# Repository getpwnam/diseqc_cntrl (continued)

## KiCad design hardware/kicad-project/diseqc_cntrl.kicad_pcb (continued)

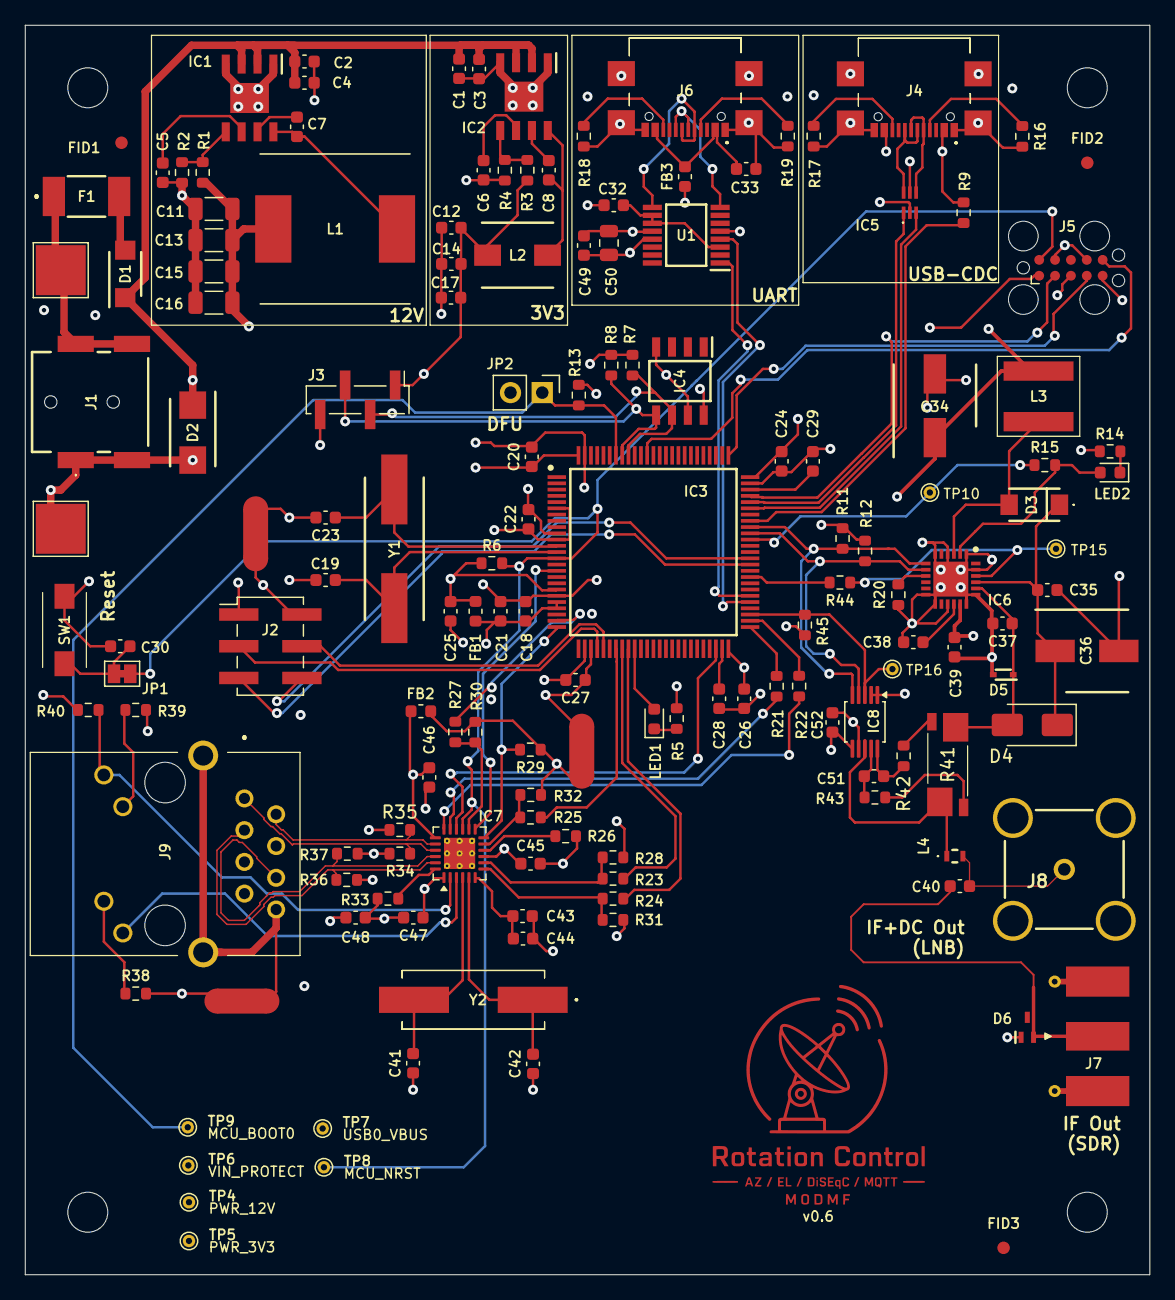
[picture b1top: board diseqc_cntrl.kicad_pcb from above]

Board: 4 copper layers, 90.0 x 100.0 mm, 153 parts (0 on the bottom side), 102 nets.

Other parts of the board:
MOUNT01, MOUNT02, MOUNT03, MOUNT04: MountingHole_3.2mm_M3

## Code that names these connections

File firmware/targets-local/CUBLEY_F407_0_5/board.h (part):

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    as safe "input + pull-up". Subsequent phases flip individual pins to their
    alternate functions as each peripheral is brought up:

      Phase 1  PD8/PD9 USART3 (AF7)              wire protocol @ 921600
      Phase 2  PB0 LED_STATUS (output PP low)    boot double-flash
      Phase 3  PB6/PB7 I2C1 (AF4 OD)             FRAM
      Phase 6  PA8/PC9 I2C3 (AF4 OD), PC8 input  LNBH26 + fault
      Phase 7  PA1/PA2/PA7/PB11-13/PC1/PC4/PC5   RMII to LAN8742A (AF11)
      Later    PD12/PD14/PD15 TIM4 (AF2)         DiSEqC carrier, motor
*/

#ifndef BOARD_H
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/* IO pins assignments.                                                      */
/*===========================================================================*/

/* GPIOA: PA1/PA2/PA7 RMII, PA8 I2C3_SCL, PA9 VBUS_SENSE, PA13/PA14 SWD */
#define GPIOA_PIN0                  0U
#define GPIOA_RMII_REF_CLK          1U
#define GPIOA_RMII_MDIO             2U
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#define GPIOA_SWCLK                 14U
#define GPIOA_PIN15                 15U

/* GPIOB: PB0 LED, PB3 SWO, PB6/PB7 I2C1, PB11-PB13 RMII TX */
#define GPIOB_LED_STATUS            0U
#define GPIOB_PIN1                  1U
#define GPIOB_PIN2                  2U
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#define GPIOB_PIN14                 14U
#define GPIOB_PIN15                 15U

/* GPIOC: PC1/PC4/PC5 RMII, PC8 LNB fault, PC9 I2C3_SDA */
#define GPIOC_PIN0                  0U
#define GPIOC_RMII_MDC              1U
#define GPIOC_PIN2                  2U
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#define GPIOC_PIN14                 14U
#define GPIOC_PIN15                 15U

/* GPIOD: PD8/PD9 USART3 (wire protocol), PD12/PD14/PD15 TIM4 */
#define GPIOD_PIN0                  0U
#define GPIOD_PIN1                  1U
#define GPIOD_PIN2                  2U
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#define GPIOE_PIN14                 14U
#define GPIOE_PIN15                 15U

/* GPIOH: only PH0/PH1 exist on LQFP100 (HSE crystal) */
#define GPIOH_OSC_IN                0U
#define GPIOH_OSC_OUT               1U
#define GPIOH_PIN2                  2U
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 * PUPDR/ODR/AFRL/AFRH encoding.
 *
 * Phase 0 rule: every board-owned peripheral pin is configured as INPUT with
 * PULL-UP so unowned peripherals cannot drive anything. Only SWD (PA13/PA14),
 * SWO (PB3), and OSC (PH0/PH1) are wired to their standard functions from
 * day one.
 */
#define PIN_MODE_INPUT(n)           (0U << ((n) * 2U))
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 * GPIOA setup (Phase 0): all peripheral pins input pull-up; SWD active.
 *
 *  PA0  - PIN0             (input pull-up)
 *  PA1  - RMII_REF_CLK     (alternate 11)
 *  PA2  - RMII_MDIO        (alternate 11, pull-up)
 *  PA3  - PIN3             (input pull-up)
 *  PA4  - PIN4             (input pull-up)
 *  PA5  - PIN5             (input pull-up)
 *  PA6  - PIN6             (input pull-up)
 *  PA7  - RMII_CRS_DV      (alternate 11)
 *  PA8  - I2C3_SCL         (input pull-up, Phase 6 -> AF4 OD)
 *  PA9  - VBUS_SENSE       (input floating, VBUS through 100k series resistor)
 *  PA10 - PIN10            (input floating)
 *  PA11 - USB_FS_DM        (alternate 10)
 *  PA12 - USB_FS_DP        (alternate 10)
 *  PA13 - SWDIO            (alternate 0)
 *  PA14 - SWCLK            (alternate 0)
 *  PA15 - PIN15            (input pull-up)
 */
#define VAL_GPIOA_MODER             (PIN_MODE_INPUT(GPIOA_PIN0)          |  \
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                                     PIN_AFIO_AF(GPIOA_SWCLK, 0U))

/*
 * GPIOB setup (Phase 0): all peripheral pins input pull-up; SWO active.
 *
 *  PB0  - LED_STATUS       (input pull-up, Phase 2 -> output PP low)
 *  PB1  - PIN1             (input pull-up)
 *  PB2  - PIN2             (input pull-up)
 *  PB3  - SWO              (alternate 0)
 *  PB4  - PIN4             (input pull-up)
 *  PB5  - PIN5             (input pull-up)
 *  PB6  - I2C1_SCL         (input pull-up, Phase 3 -> AF4 OD)
 *  PB7  - I2C1_SDA         (input pull-up, Phase 3 -> AF4 OD)
 *  PB8  - PIN8             (input pull-up)
 *  PB9  - PIN9             (input pull-up)
 *  PB10 - PIN10            (input pull-up)
 *  PB11 - RMII_TX_EN       (alternate 11, pull-down)
 *  PB12 - RMII_TXD0        (alternate 11, pull-down)
 *  PB13 - RMII_TXD1        (alternate 11, pull-down)
 *  PB14 - PIN14            (input pull-up)
 *  PB15 - PIN15            (input pull-up)
 */
#define VAL_GPIOB_MODER             (PIN_MODE_INPUT(GPIOB_LED_STATUS)    |  \
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 * GPIOC setup (Phase 0): all peripheral pins input pull-up.
 *
 *  PC0  - PIN0             (input pull-up)
 *  PC1  - RMII_MDC         (alternate 11, pull-up)
 *  PC2  - PIN2             (input pull-up)
 *  PC3  - PIN3             (input pull-up)
 *  PC4  - RMII_RXD0        (alternate 11)
 *  PC5  - RMII_RXD1        (alternate 11)
 *  PC6  - PIN6             (input pull-up)
 *  PC7  - PIN7             (input pull-up)
 *  PC8  - LNB_FLT          (input pull-up)
 *  PC9  - I2C3_SDA         (input pull-up, Phase 6 -> AF4 OD)
 *  PC10 - PIN10            (input pull-up)
 *  PC11 - PIN11            (input pull-up)
 *  PC12 - PIN12            (input pull-up)
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 * GPIOD setup (Phase 0): all peripheral pins input pull-up.
 *
 *  PD0..PD7   PIN0..PIN7   (input pull-up)
 *  PD8  - USART3_TX        (input pull-up, Phase 1 -> AF7)
 *  PD9  - USART3_RX        (input pull-up, Phase 1 -> AF7)
 *  PD10 - PIN10            (input pull-up)
 *  PD11 - PIN11            (input pull-up)
 *  PD12 - TIM4_CH1         (input pull-up, later -> AF2)
 *  PD13 - PIN13            (input pull-up)
 *  PD14 - TIM4_CH3         (input pull-up, later -> AF2)
 *  PD15 - TIM4_CH4         (input pull-up, later -> AF2)
 */
#define VAL_GPIOD_MODER             0x00000000U
#define VAL_GPIOD_OTYPER            0x00000000U
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#define VAL_GPIOG_AFRH              0x00000000U

/*
 * GPIOH setup (LQFP100): only PH0 (OSC_IN) and PH1 (OSC_OUT) are pinned out.
 * ChibiOS PAL leaves them as input floating; the stm32_clock_init() code
 * enables the HSE oscillator via RCC->CR (BYP=0, HSEON=1).
 */
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
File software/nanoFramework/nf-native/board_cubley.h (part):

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 * Board identifier
 */
#define BOARD_M0DMF_CUBLEY_F407
#define BOARD_NAME                  "DiSEqC Controller STM32F407VGT6"

/*
 * USB OTG_FS configuration.
 *
 * The board exposes USB VBUS to PA9 only through R31 (100k pull-up to VBUS,
 * no divider/pull-down). That impedance is too high to reliably trip the
 * STM32F407 OTG_FS A/B-session VBUS comparators, so VBUSASEN/VBUSBSEN never
 * report VBUS valid, the core never asserts the D+ pull-up, and the host
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/*
 * DiSEqC Configuration
 */
#define DISEQC_PWM_DRIVER           PWMD4    // TIM4 for DiSEqC carrier
#define DISEQC_GPT_DRIVER           GPTD5    // TIM5 for bit timing
#define DISEQC_OUTPUT_LINE          PAL_LINE(GPIOD, 12U)  // PD12 = TIM4_CH1

// Note: No motor enable pin - LNBH26 handles power control automatically
// DiSEqC commands control rotor movement directly
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 * LNB Control Configuration (LNBH26PQR via I2C)
 * 
 * LNBH26PQR is controlled via I2C interface:
 * - I2C3: PA8 (SCL), PC9 (SDA)
 * - I2C Address: 0x08 (7-bit)
 * 
 * The LNBH26PQR controls:
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
/*
 * RMII Ethernet Configuration (hardware v0.5)
 * PA1  = REF_CLK
 * PA2  = MDIO
 * PA7  = CRS_DV
 * PC1  = MDC
 * PC4  = RXD0
 * PC5  = RXD1
 * PB11 = TX_EN
 * PB12 = TXD0
 * PB13 = TXD1
 */
#define ETH_RMII_REF_CLK_LINE       PAL_LINE(GPIOA, 1U)
#define ETH_RMII_MDIO_LINE          PAL_LINE(GPIOA, 2U)
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/*
 * Rotator helper signal mapping (feature bring-up)
 */
#define ROTATOR_PWM_A_LINE          PAL_LINE(GPIOD, 14U) // TIM4_CH3
#define ROTATOR_PWM_B_LINE          PAL_LINE(GPIOD, 15U) // TIM4_CH4
#define ROTATOR_ADC_A_LINE          PAL_LINE(GPIOA, 4U)  // ADC1_IN4
#define ROTATOR_ADC_B_LINE          PAL_LINE(GPIOA, 5U)  // ADC1_IN5

/*
 * IO pins assignments
 */
#define GPIOA_PIN0                  0U  // Adjust to your schematic
#define GPIOA_PIN1                  1U
#define GPIOA_PIN2                  2U  // MDIO
#define GPIOA_PIN3                  3U
#define GPIOA_PIN4                  4U
#define GPIOA_PIN5                  5U
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#define GPIOB_PIN3                  3U
#define GPIOB_PIN4                  4U
#define GPIOB_PIN5                  5U
#define GPIOB_PIN6                  6U  // I2C1_SCL
#define GPIOB_PIN7                  7U  // I2C1_SDA
#define GPIOB_PIN8                  8U
#define GPIOB_PIN9                  9U
#define GPIOB_PIN10                 10U
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#define GPIOC_PIN5                  5U  // RMII_RXD1
#define GPIOC_PIN6                  6U
#define GPIOC_PIN7                  7U
#define GPIOC_PIN8                  8U  // LNB_FLT
#define GPIOC_PIN9                  9U  // I2C3_SDA (LNBH26)
#define GPIOC_PIN10                 10U
#define GPIOC_PIN11                 11U
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#define GPIOD_PIN5                  5U
#define GPIOD_PIN6                  6U
#define GPIOD_PIN7                  7U
#define GPIOD_PIN8                  8U  // USART3_TX
#define GPIOD_PIN9                  9U  // USART3_RX
#define GPIOD_PIN10                 10U
#define GPIOD_PIN11                 11U
#define GPIOD_PIN12                 12U  // TIM4_CH1 (DiSEqC output)
#define GPIOD_PIN13                 13U
#define GPIOD_PIN14                 14U // TIM4_CH3
#define GPIOD_PIN15                 15U // TIM4_CH4

/*
 * I/O ports initial setup, this configuration is established soon after reset
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
/*
 * GPIOA setup:
 * PA1  - Alternate RMII_REF_CLK
 * PA2  - Alternate RMII_MDIO
 * PA4  - Analog ADC1_IN4
 * PA5  - Analog ADC1_IN5
 * PA7  - Alternate RMII_CRS_DV
 * PA8  - Alternate I2C3_SCL
 */
#define VAL_GPIOA_MODER             (PIN_MODE_ALTERNATE(GPIOA_PIN1) |           \
                                     PIN_MODE_ALTERNATE(GPIOA_PIN2) |           \
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
/*
 * GPIOB setup:
 * PB0  - Output (LED_STATUS)
 * PB6  - Alternate I2C1_SCL
 * PB7  - Alternate I2C1_SDA
 * PB11 - Alternate RMII_TX_EN
 * PB12 - Alternate RMII_TXD0
 * PB13 - Alternate RMII_TXD1
 */
#define VAL_GPIOB_MODER             (PIN_MODE_OUTPUT(GPIOB_PIN0) |              \
                                     PIN_MODE_ALTERNATE(GPIOB_PIN6) |           \
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
/*
 * GPIOC setup:
 * PC1 - Alternate RMII_MDC
 * PC4 - Alternate RMII_RXD0
 * PC5 - Alternate RMII_RXD1
 * PC8 - Input (LNB_FLT)
 * PC9 - Alternate I2C3_SDA
 */
#define VAL_GPIOC_MODER             (PIN_MODE_ALTERNATE(GPIOC_PIN1) |           \
                                     PIN_MODE_ALTERNATE(GPIOC_PIN4) |           \
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
/*
 * GPIOD setup:
 * PD8  - Alternate USART3_TX
 * PD9  - Alternate USART3_RX
 * PD12 - Alternate TIM4_CH1 (DiSEqC output)
 * PD14 - Alternate TIM4_CH3 (rotator PWM A)
 * PD15 - Alternate TIM4_CH4 (rotator PWM B)
 */
#define VAL_GPIOD_MODER             (PIN_MODE_ALTERNATE(GPIOD_PIN8) |           \
                                     PIN_MODE_ALTERNATE(GPIOD_PIN9) |           \
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
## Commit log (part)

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2026-02-09 Clean up nonfree directory before adding submodule
2026-02-09 Add nonfree KiCad assets submodule
2026-02-09 Updated project library paths
2026-02-09 Pinned newer version of nonfree
2026-02-09 Added licensing info
2026-02-11 Add MCU pin check tool
2026-02-12 First software commit
2026-02-22 Remove BOM/Stock list
2026-02-22 Added test points for power regulation
2026-02-22 Added more test points
2026-02-22 Clean up PCB library paths
2026-02-23 Bugfix: mcu_check_pins.py reports unlabelled nets as floating
2026-02-23 software changes to handle TIM1->TIM4 pin migration
2026-02-23 feat(nanoframework): add profile-driven nf-interpreter build integration
2026-02-23 tools: remove hard-coded home path in mcu pin checker
2026-02-23 Update nonfree submodule pointer to 95c5a8c
2026-02-23 Add runtime config persistence and toolchain scripts
2026-02-23 Fix nf-interpreter build on fresh clone
    - Remove malformed duplicate block in w5500 interop native source
    - Add ConfigPins_I2C3 stub to satisfy linker in Docker build
    - Document stub follow-up in nanoFramework TODO
2026-02-23 Fix managed package reference paths for fresh clones
    Use DiSEqC_Control/packages hint paths so compile-managed works after NuGet restore in a clean checkout.
2026-02-23 Add managed unit test docs and initial host test suite
    - Document unit-test commands in nanoFramework README
    - Add xUnit host test project for RuntimeConfiguration and ParityHelper
    - Update TODO with managed/interop test coverage milestones
2026-02-23 Add phased implementation plan to TODO
    Document agreed sequence: managed tests, interop contracts, W5500 native transport, USB wire protocol migration, and hardware validation.
2026-02-23 Pause Phase 2 test expansion and activate Phase 3
    Mark additional host-side test construction as paused and set real W5500 native transport as active focus.
2026-02-23 Wire W5500 runtime config into native transport and add tests
2026-02-24 Add beginner-friendly DiSEqC signal generation explanation
2026-02-24 Complete Phase 3.5 MQTT W5500 adapter integration
2026-03-06 Corrected 3v3 reg component layout
2026-03-06 Remove old gerber location
2026-03-24 Added ground pad for easier testing
2026-03-31 Fix: VBAT should be connected to VDD
2026-03-31 Fix: Add VBUS sense to MCU for USB DFU
2026-04-02 fix(nanoBooter): use HSI PLL on all profiles — no HSE crystal fitted
    RCC_CR=0x7C83 confirmed via GDB: PLLON=0, HSEON=0. ChibiOS
    stm32_clock_init() was spinning on HSERDY at 0x08002530 because
    mcuconf.h had STM32_HSE_ENABLED TRUE / STM32_PLLSRC_HSE. With no HSE
    crystal the bit never sets, so nanoBooter hangs in clock init and
    never calls LaunchCLR().
    Changes:
2026-04-02 fix(build): apply custom mcuconf before profile overrides
    Move /work/build/mcuconf.h copy step earlier so board/profile override blocks
    remain final. Previously mcuconf copy happened after overrides, silently
    clobbering generated settings (RTC source, MAC/USB/profile flags, etc.).
2026-04-02 fix(nanoBooter): disable HAL RTC in booter startup
    nanoBooter does not require RTC. Force HAL_USE_RTC=FALSE for
    nanoBooter halconf generation to avoid early RTC init loops blocking
    handoff to nanoCLR on boards with backup-domain clock/source variance.
    nanoCLR still follows profile RTC setting.
2026-04-03 fix(uart): force PB10/PB11 AF7 for USART3 before sdStart
    E2002 triage showed USART3 peripheral configured but GPIOB mux registers not
    matching PB10/PB11 AF7 runtime expectation. Add a direct register-level safety
    path in nanoCLR main to enable GPIOB clock and force PB10/PB11 to AF7 before
    starting SERIAL_DRIVER.
2026-04-03 fix(build): full clean on profile change to prevent contaminated binaries
    When switching between build profiles (e.g. bringup-smoke -> minimal or
    vice versa), incremental builds reuse cached .o files from the previous
    profile. This produces binaries whose vector-table reset-handler address
    points outside the new binary, causing an immediate crash on boot with
    no serial output.
    Add profile-change detection: store last profile in .last_profile marker
2026-04-07 Fix nanoFramework bring-up and deployment flow
2026-04-08 nanoFramework bring-up: fix GPIOA startup and harden managed deploy tooling
2026-04-08 Added USB-UART instead of board headers
2026-04-08 vendor all target-overrides; remove ST_STM32F4_DISCOVERY reference dependency
    Vendor the full set of target files previously backfilled at build time
    from the nf-interpreter ST_STM32F4_DISCOVERY reference board into
    nf-native/target-overrides/:
    common/ - Device_BlockStorage.c, usbcfg.c/h
    nanoCLR/ - halconf.h, halconf_nf.h, chconf.h, main.c,
    target_board.h.in, STM32F407xG_CLR.ld
2026-04-08 Fix usb-no-vbus board.h rewrite line skipping
2026-04-08 Improve usb-no-vbus runtime bring-up handling
2026-04-09 Add deferred motor-control follow-up tasks
2026-04-09 WIP: checkpoint mailbox interop investigation
2026-04-10 Stabilize UART init and preflight across profiles
2026-04-10 Add interop checksum preflight and logging
2026-04-10 Remove superseded DiSEqC interop project files
2026-04-10 Add persistent native error telemetry for W5500 open failures
2026-04-10 Reverted to b90ff18: app works, Docker firmware build has CMakeLists.txt path issue
2026-04-11 Log checksum gate hardening checkpoint
2026-04-11 Log W5500 connect-stage failure checkpoint
2026-04-11 Log mailbox connect failure with PHY-down snapshot
2026-04-11 w5500: harden PHY reset sequencing and capture diag checkpoints
2026-04-11 board: enable GPIOB and GPIOC AHB1 clocks in boardInit
    GPIOA was the only port clocked, so any pin on port B or C silently
    failed to drive. PC6 (W5500 reset) and PB10/PB11 (SPI/diagnostic)
    were both deaf to palSetLine/palToggleLine as a result.
    Add GPIOBEN and GPIOCEN alongside the existing GPIOAEN.
2026-05-05 W5500 bring-up: autoneg works, TCP established, diag cleanup
    Bring the W5500/MQTT interface up end-to-end on M0DMF_CUBLEY_F407.
    Hardware context (recorded for posterity, no PCB respin in this commit):
    - Reverted ad-hoc 75 ohm pulls from 3V3 to PHY-side centre taps CT_1/CT_2 -
    these were never on the WIZnet reference and were loading the TX bias
    network. Real Bob-Smith network (75R+75R+1nF on cable-side CT_3/CT_4) is
    parked for the next PCB revision; bench uses an intermediate switch to
2026-05-12 Fix CLR startup type resolution and retain regression diagnostics
    - identify ResolveAll failure owner/missing assembly via temporary pointer diagnostics
    - include nanoFramework.Runtime.Events in managed deployment path
    - keep StartupProbe active and add TODO note to remove temporary diagnostics later
    - append bring-up validation results
2026-05-12 Refactor managed interop and startup flow
    - align Cubley.Interop native declarations and assembly metadata
    - adjust DiSEqC managed startup path and LNB native binding usage
2026-05-13 Add hardware presence probes for W5500, LNBH26, and FRAM
    - Implement StartupProbe.cs with three separate bus-level probes:
    - W5500: SPI-based via NativeOpen/NativeGetVersion
    - LNBH26: I2C1 direct address probe (0x08)
    - FRAM: I2C3 direct address probe (0x50)
    - Probes execute at startup and report bitmap status (0x06 in this board config)
    - Add startup breadcrumb markers (0xD5E1xxxx) for scope/SWD correlation
2026-05-13 Log: Successful hardware probe validation via scope capture
    Documented probe results confirming:
    - W5500 absent (not soldered on board)
    - LNBH26 present on I2C1
    - FRAM present on I2C3 with clean transaction framing
    Scope capture confirms full I2C3 FRAM write-read sequence with ACK/NACK
    handling, bus clock ~350-400 kHz, no electrical faults observed.
2026-05-13 Keep only DiSEqC_Control managed app
2026-05-19 Removed separate VDDA/VSSA planes
2026-05-19 Added FT230X decoupling (C44)
2026-05-20 Added test points for I2C1 (2)
2026-05-26 Locking hw ver 0.4
2026-05-26 Refactor diagnostics mailbox and add boot-probe latch docs
2026-05-26 Add end-to-end LNBH26 control path
    Implement native LNB init/status APIs, wire new interop bindings, integrate managed command handling, and add bring-up probe/log checkpoints for hardware validation.
2026-06-04 Added devcontainer config
2026-06-04 Remove hardcoded paths in build chain
2026-06-04 Add debugging tools to devcontainer
2026-06-05 Add iproute2 to devcontainer
2026-06-05 feat: add profile-aware native pin configuration checks
2026-06-05 Reorganize docs and unify nanoFramework build scripts
2026-06-05 Fix ambiguous discovery handling in build-managed
2026-06-05 chore: sync profile coverage test and remove pycache artifacts
2026-06-05 test: harden build.sh profile list extraction
2026-06-05 test: use deterministic parsing for build profile sync check
2026-06-05 Add interop CI guard and enforce native-only Cubley.Interop
2026-06-05 Add reusable PR body formatting skill
2026-06-05 Make startup W5500 probe presence-only
2026-06-06 Add stable firmware phase umbrella tracker checklist
2026-06-07 Phase A: Lock baseline build and flash configuration
    - Add docs/debug/PHASE_A_BASELINE.md: canonical Phase A baseline reference
    covering selected build profile (cubley-stable), accurate flash map,
    pinned tooling versions, baseline wiring, host setup assumptions, and
    non-baseline run marking convention.
    - Add --baseline yes|no flag to bringup_log_append.sh: non-baseline entries
    get a [NON-BASELINE] annotation and an explanatory Baseline field.
2026-06-07 Phase A baseline: reflect devcontainer as the execution environment
    All dev/build/flash work runs inside the devcontainer; no Docker Compose,
    host-side nanoff, or host-side stlink-tools are required.
    - PHASE_A_BASELINE.md: replace Docker Compose / host-tools tooling table
    with the devcontainer pinned versions (gcc-arm-none-eabi 15.2.rel1,
    cmake 3.31.6); replace host setup assumptions with devcontainer setup
    (open container, USB passthrough); update References to point at
2026-06-07 Implement deterministic startup probe markers and aggregate status latch
2026-06-07 Standardize Phase A status decoding and contract docs
2026-06-07 Harden Phase A reader validation and shared decode mapping
2026-06-07 Define Phase A exit gate
2026-06-07 Added oscilloscope skill
2026-06-07 Move CMakeLists.txt to static file, enforce NF_STATIC_AUDIT=1 for cubley-stable, update ARCHITECTURE.md
2026-06-07 Record 20/20 PASS deterministic flash-reset campaign (issue #26)
2026-06-07 Document Phase A exit freeze and Phase B handoff
2026-06-07 Phase B interop governance guards and policy docs
2026-06-07 Harden Tier-0 diagnostics mailbox latch semantics
2026-06-08 Establish cubley-base baseline and deprecate legacy profiles by default
2026-06-08 Removing reference to cubley-stable in docs, bugfixes in build-native.sh
2026-06-08 Rebaseline Phase B governance to cubley-base
2026-06-08 Refactor probe retries to return status
2026-06-08 Log issue #26 deterministic campaign rerun
2026-06-08 Address PR #58 review: reap OpenOCD and isolate Tier-1 result
2026-06-08 Phase C #48: define normative Tier-0/Tier-1 encoding semantics
2026-06-08 Address PR #59 review: clarify stage/error semantics and markdown formatting
2026-06-08 Phase C #49: add strict Tier-0/Tier-1 reset-cycle gate
2026-06-08 cubley-base: configure PA2 LED as output low
2026-06-08 Fix Phase C strict smoke by disabling CLR startup patching in stable profile
2026-06-09 chore: checkpoint W5500 smoke bringup work
2026-06-09 Corrected TP20 value
2026-06-18 Added MCU decoupling
2026-06-19 Ethernet routing
2026-06-23 Placed LNBH26
